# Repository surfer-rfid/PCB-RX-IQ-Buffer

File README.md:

# PCB-RX-IQ-Buffer
Kicad project for RX I/Q digital signal and clock buffer board for logic analyzer buffering.

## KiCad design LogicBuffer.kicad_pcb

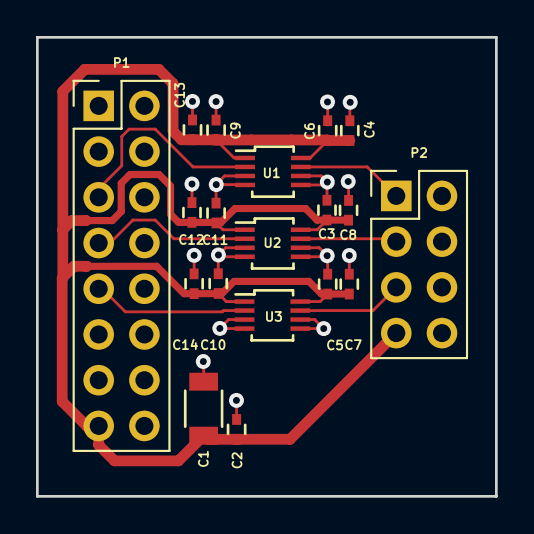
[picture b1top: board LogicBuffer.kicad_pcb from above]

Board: 2 copper layers, 25.5 x 25.5 mm, 19 parts (0 on the bottom side), 8 nets.

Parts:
C1: 10u; C_1206
C2: 1u; C_0402
C3, C4, C5, C9, C10, C11: 100p; C_0402
C6, C7, C8, C12, C13, C14: 100n; C_0402
P1: CONN_02X08; Pin_Header_Straight_2x08_Pitch2.54mm
P2: CONN_02X04; Pin_Header_Straight_2x04_Pitch2.54mm
U1, U2, U3: 74AXP2T3407; VSSOP-8_2p1x2p4mm_Pitch0.5mm

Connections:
/CLK_36_IN: P1.9, U3.2
/CLK_36_OUT: P2.5, U3.7
/FPGA_I_IN_IN: P1.5, U1.2
/FPGA_I_IN_OUT: P2.1, U1.7
/FPGA_Q_IN_IN: P1.7, U2.2
/FPGA_Q_IN_OUT: P2.3, U2.7
GND: C1.2, C2.2, C3.2, C4.2, C5.2, C6.2, C7.2, C8.2, C9.1, C10.2, C11.2, C12.2, C13.2, C14.2, P1.2, P1.4, P1.6, P1.8, P1.10, P1.12, P1.14, P1.16, P2.2, P2.4, P2.6, P2.8, U1.3, U1.4, U1.5, U1.6, U2.3, U2.4, U2.5, U2.6, U3.3, U3.4, U3.5, U3.6
VDD: C1.1, C2.1, C3.1, C4.1, C5.1, C6.1, C7.1, C8.1, C9.2, C10.1, C11.1, C12.1, C13.1, C14.1, P1.15, P2.7, U1.1, U1.8, U2.1, U2.8, U3.1, U3.8

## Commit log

2021-01-30 Add files for first time.
    Add RX IQ buffer files for the first time.

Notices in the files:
LogicBuffer.kicad_pcb:
Licensed under CERN-OHL-P v2 or later.
Copyright 2021 Superlative Semiconductor LLC.
